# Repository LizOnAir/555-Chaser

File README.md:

# 555-Chaser
I made this project to learn about analog sensors.

## Feature
A butterfly shape PCB board that have 10 LEDs.

## PCB
Schematic

Layout

## BOM
Here should be [everything]([https://docs.google.com/spreadsheets/d/1zaCOEk-ZGnszMIk4FFVV_LndeX-SJLxj8WLiJESGuGM/edit?gid=0#gid=0](https://docs.google.com/spreadsheets/d/1AuRfUaX59UFpKWCV63FwTXzQ7sGg3CwstVuxbCmtyvM/edit?usp=sharing)) you need:
- 1x PCB
- 10x LEDs
- 1x Timer Ic (NE555P)
- 1x IO expander ()CD4017
- 1x Potentiometer
- 1x 470ohm resistor
- 1x capacitor
- 1x polarized capacitor

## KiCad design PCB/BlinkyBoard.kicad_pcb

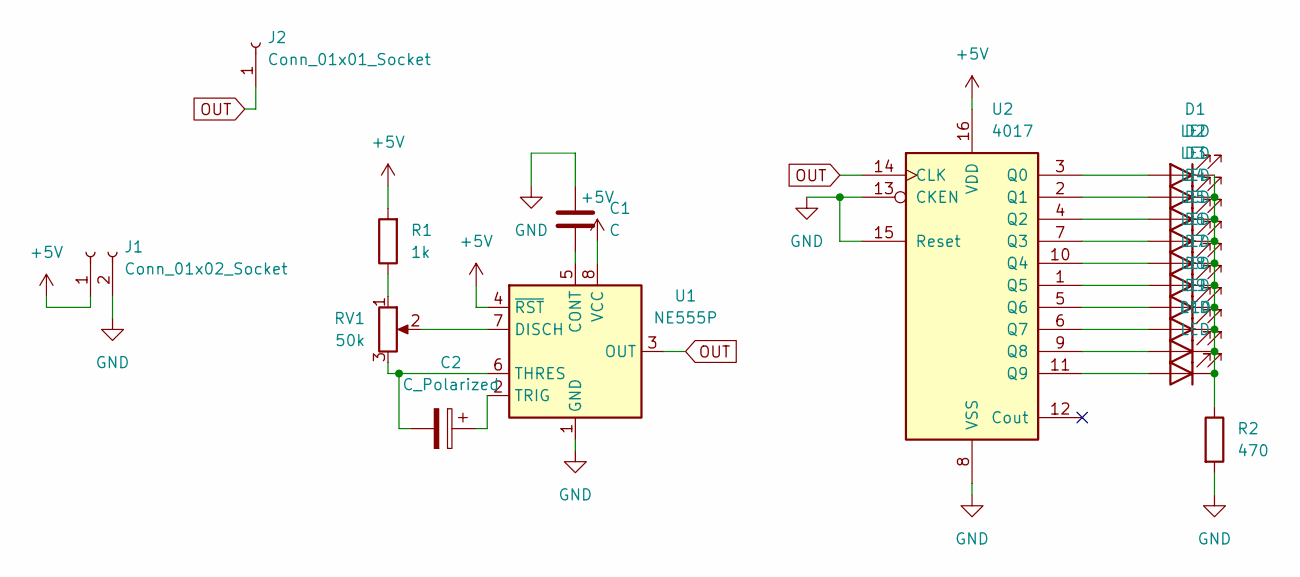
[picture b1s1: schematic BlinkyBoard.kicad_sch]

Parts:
C1: C; C_Disc_D7.5mm_W2.5mm_P5.00mm
C2: C_Polarized; CP_Radial_D5.0mm_P2.00mm
D1, D2, D3, D4, D5, D6, D7, D8, D9, D10: LED; LED_D3.0mm
J1: Conn_01x02_Socket; PinHeader_1x02_P2.54mm_Vertical
J2: Conn_01x01_Socket; PinHeader_1x01_P2.54mm_Vertical
R1: 1k; R_Axial_DIN0207_L6.3mm_D2.5mm_P7.62mm_Horizontal
R2: 470; R_Axial_DIN0207_L6.3mm_D2.5mm_P7.62mm_Horizontal
RV1: 50k; Potentiometer_Runtron_RM-065_Vertical
U1: NE555P; DIP-8_W7.62mm
U2: 4017; N16

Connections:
+5V: J1.1, R1.2, U1.4 (~RST), U1.8 (VCC), U2.16 (VDD)
GND: C1.1, J1.2, R2.2, U1.1 (GND), U2.8 (VSS), U2.13 (CKEN), U2.15 (Reset)
unnamed: D1.2 (A), U2.3 (Q0)
unnamed: D1.1 (K), D2.1 (K), D3.1 (K), D4.1 (K), D5.1 (K), D6.1 (K), D7.1 (K), D8.1 (K), D9.1 (K), D10.1 (K), R2.1
unnamed: D2.2 (A), U2.2 (Q1)
unnamed: D3.2 (A), U2.4 (Q2)
unnamed: D4.2 (A), U2.7 (Q3)
unnamed: D5.2 (A), U2.10 (Q4)
unnamed: D6.2 (A), U2.1 (Q5)
unnamed: D7.2 (A), U2.5 (Q6)
unnamed: D8.2 (A), U2.6 (Q7)
unnamed: D9.2 (A), U2.9 (Q8)
unnamed: D10.2 (A), U2.11 (Q9)
unnamed: R1.1, RV1.1
unnamed: C1.2, U1.5 (CONT)
unnamed: RV1.2, U1.7 (DISCH)
unnamed: C2.2, RV1.3, U1.6 (THRES)
unnamed: C2.1, U1.2 (TRIG)
OUT: J2.1, U1.3 (OUT), U2.14 (CLK)

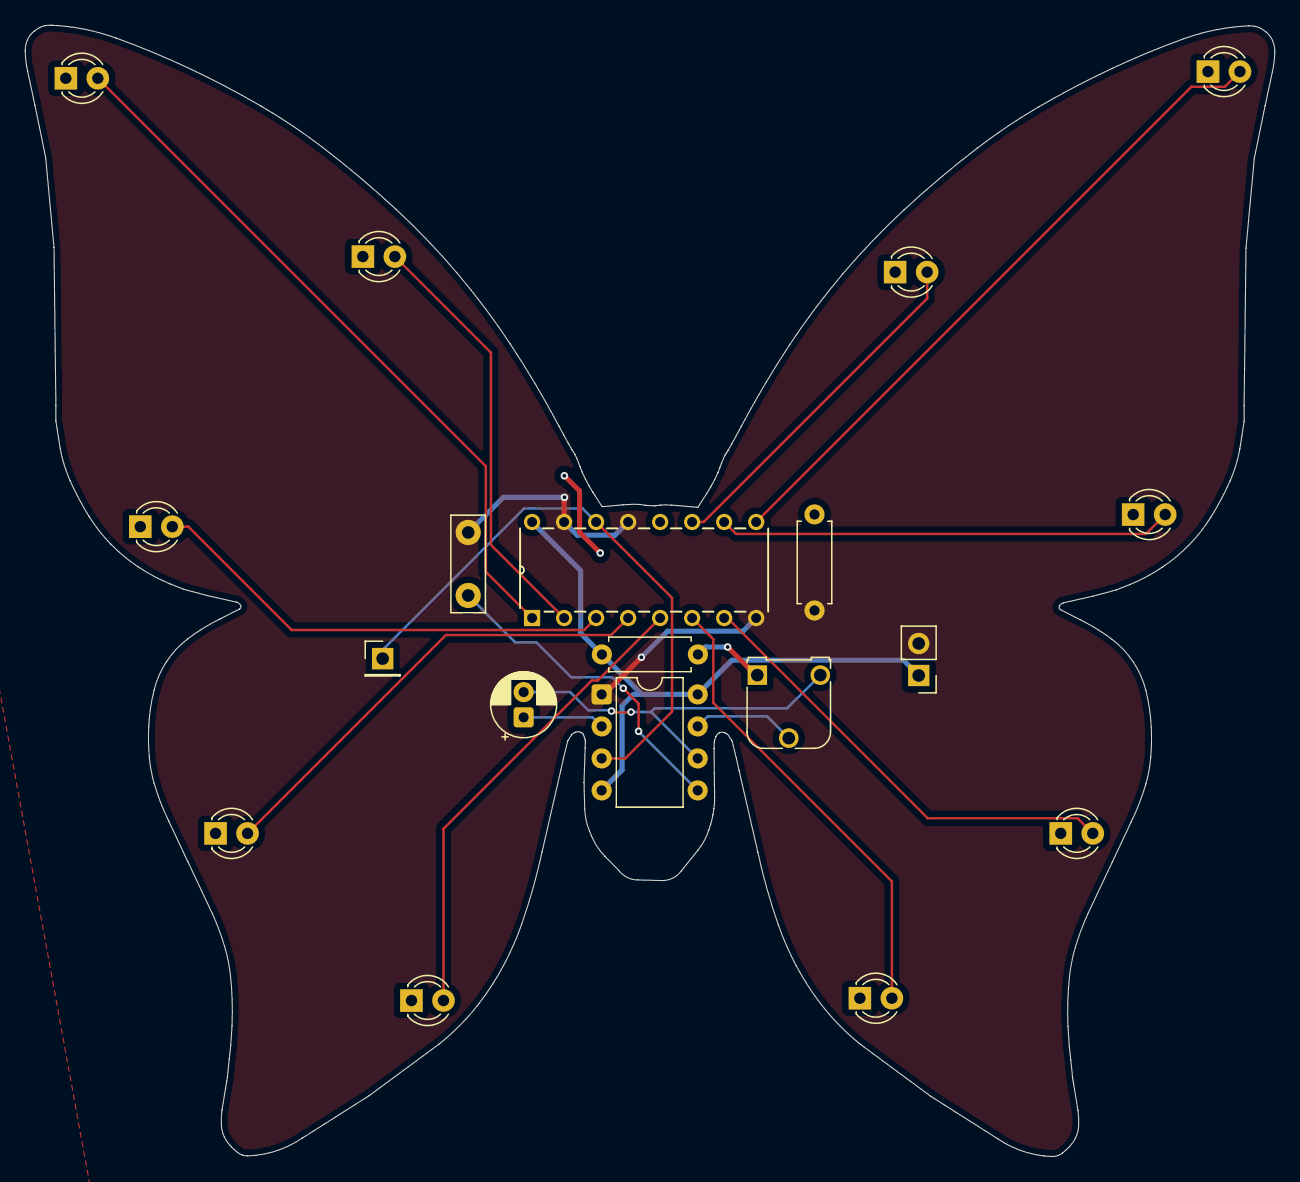
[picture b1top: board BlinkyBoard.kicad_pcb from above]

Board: 2 copper layers, 99.2 x 89.8 mm, 19 parts (0 on the bottom side), 19 nets.

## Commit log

2026-04-13 Rename BlinkyBoard.kicad_pcb to PCB/BlinkyBoard.kicad_pcb
2026-04-13 Rename BlinkyBoard - Sheet1.csv to BlinkyBoardBOM- Sheet1.csv
